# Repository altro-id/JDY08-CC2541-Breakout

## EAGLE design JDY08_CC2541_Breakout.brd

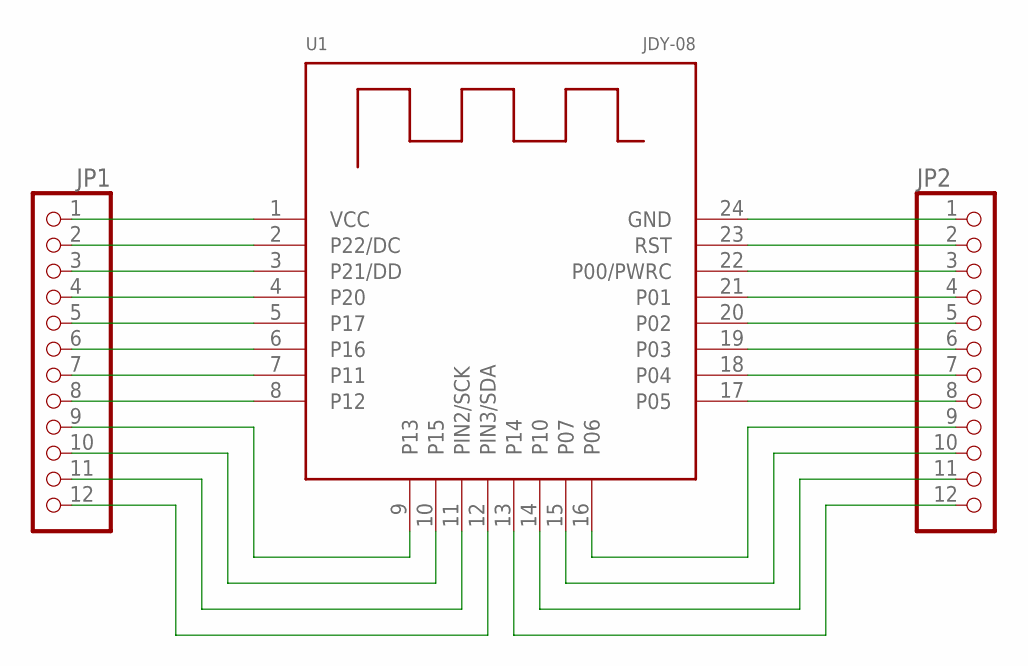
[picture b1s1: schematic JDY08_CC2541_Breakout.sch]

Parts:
JP1, JP2: HEADER-1X1276MIL; 1X12_ROUND_76MIL
U1: JDY-08

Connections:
unnamed: JP1.1, U1.1 (VCC)
unnamed: JP1.2, U1.2 (P22/DC)
unnamed: JP1.3, U1.3 (P21/DD)
unnamed: JP1.4, U1.4 (P20)
unnamed: JP1.5, U1.5 (P17)
unnamed: JP1.6, U1.6 (P16)
unnamed: JP1.7, U1.7 (P11)
unnamed: JP1.8, U1.8 (P12)
unnamed: JP2.1, U1.24 (GND)
unnamed: JP2.2, U1.23 (RST)
unnamed: JP2.3, U1.22 (P00/PWRC)
unnamed: JP2.4, U1.21 (P01)
unnamed: JP2.5, U1.20 (P02)
unnamed: JP2.6, U1.19 (P03)
unnamed: JP2.7, U1.18 (P04)
unnamed: JP2.8, U1.17 (P05)
unnamed: JP1.9, U1.9 (P13)
unnamed: JP1.10, U1.10 (P15)
unnamed: JP1.11, U1.11 (PIN2/SCK)
unnamed: JP1.12, U1.12 (PIN3/SDA)
unnamed: JP2.9, U1.16 (P06)
unnamed: JP2.10, U1.15 (P07)
unnamed: JP2.11, U1.14 (P10)
unnamed: JP2.12, U1.13 (P14)

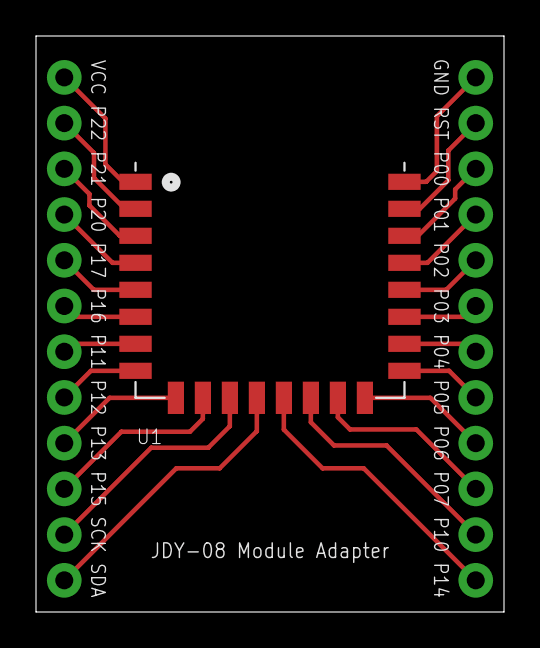
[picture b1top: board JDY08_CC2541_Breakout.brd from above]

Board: 2 copper layers, 26.0 x 32.0 mm, 3 parts (0 on the bottom side), 24 nets.

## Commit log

2017-08-10 Added Schematic and Board

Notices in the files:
parts and their libraries:
microbuilder: This work is placed in the public domain, and may be freely used for commercial and non-commercial work with the following conditions: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
